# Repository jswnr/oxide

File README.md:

# Oxide
A 60-key USB keyboard built with Raspberry Pi Pico

## Default layout
|         |      |       |      |      |       |       |       |      |      |       |               |
|---------|------|-------|------|------|-------|-------|-------|------|------|-------|---------------|
| \`      | 1 F1 | 2 F2  | 3 F3 | 4 F4 | 5 F5  | 6 F6  | 7 F7  | 8 F8 | 9 F9 | 0 F10 | Backspace F11 |
| Tab     | Q    | W     | E    | R    | T     | Y     | U     | I    | O    | P     | Delete F12    |
| Esc     | A    | S     | D    | F    | G     | H ←   | J ↓   | K ↑  | L →  | ;     | Enter         |
| Shift   | Z    | X     | C    | V    | B     | N     | M     | ,    | .    | /     | '             |
| Control | Fn   | Super | \\   | Alt  | Space | Space | AltGr | [    | ]    | -     | =             |

## Bill of materials
| Component              | Details                          | Quantity |
|------------------------|----------------------------------|----------|
| PCB                    | 1.2 mm thick                     | 1        |
| Raspberry Pi Pico      |                                  | 1        |
| Male pin header        | 2.54 mm pitch, 20 pins           | 2        |
| Cherry MX switch       |                                  | 60       |
| 1N4148 diode           | DO-35 package                    | 60       |
| Case                   | `case.scad`                      | 1        |
| Homing keycap          | `keycap_homing.scad`             | 2        |
| Space keycap           | `keycap_space.scad`              | 2        |
| Keycap                 | `keycap.scad`                    | 56       |
| M2 screw               | Pan head, 6 mm long              | 8        |
| M2 brass insert        | 6 mm long, 3.5 mm outer diameter | 8        |

## Firmware
1. Install Pico SDK and Picotool.
2. Navigate to the `firmware` directory and run:
```
mkdir build
cd build
cmake ..
make -j$(nproc)
```
3. Hold down the BOOTSEL button on the Pico while plugging it in. Then run the following commands as root:
```
picotool load firmware.uf2
picotool reboot
```

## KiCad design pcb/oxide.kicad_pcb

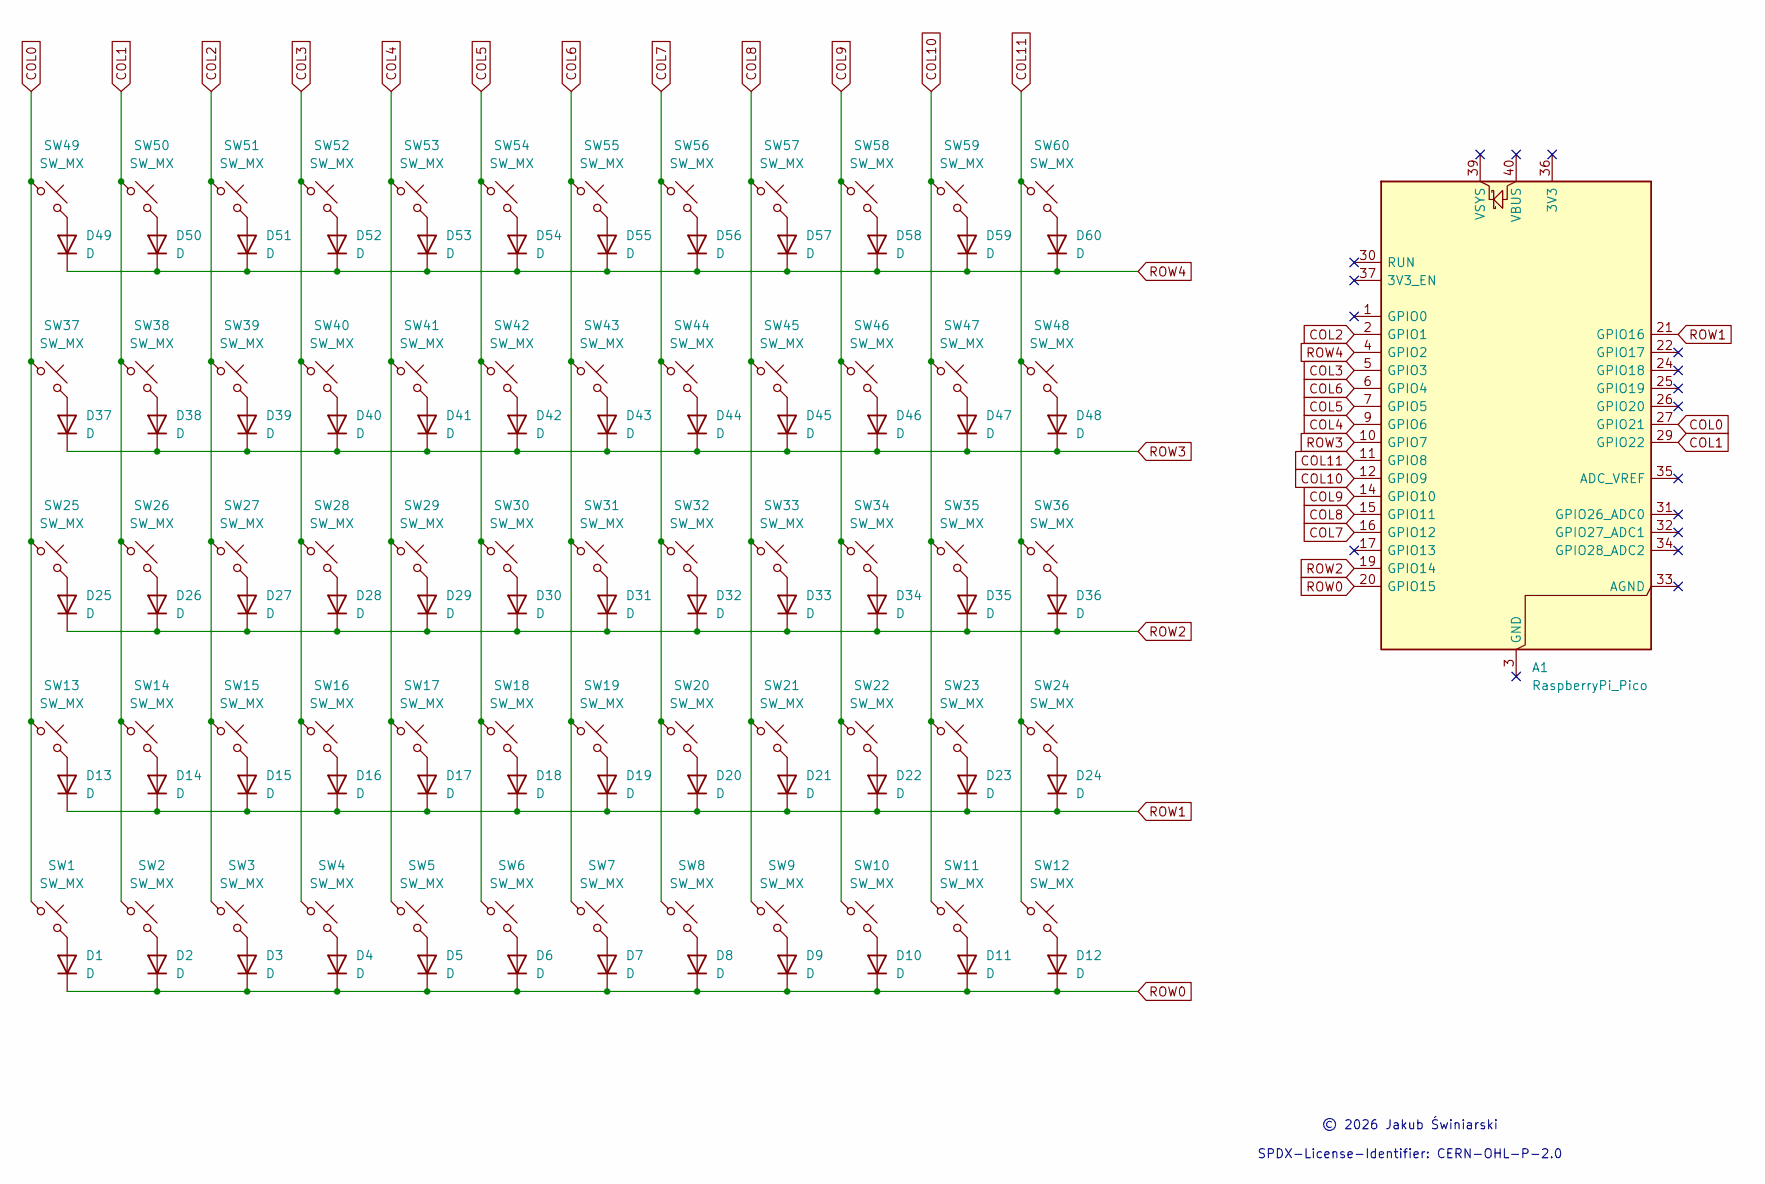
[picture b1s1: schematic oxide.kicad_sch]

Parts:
A1: RaspberryPi_Pico; RaspberryPi_Pico_Common_THT
D1, D2, D3, D4, D5, D6, D7, D8, D9, D10, D11, D12, D13, D14, D15, D16, D17, D18, D19, D20, D21, D22, D23, D24, D25, D26, D27, D28, D29, D30, D31, D32, D33, D34, D35, D36, D37, D38, D39, D40, D41, D42, D43, D44, D45, D46, D47, D48, D49, D50, D51, D52, D53, D54, D55, D56, D57, D58, D59, D60: D; D_DO-35_SOD27_P7.62mm_Horizontal
SW1, SW2, SW3, SW4, SW5, SW6, SW7, SW8, SW9, SW10, SW11, SW12, SW13, SW14, SW15, SW16, SW17, SW18, SW19, SW20, SW21, SW22, SW23, SW24, SW25, SW26, SW27, SW28, SW29, SW30, SW31, SW32, SW33, SW34, SW35, SW36, SW37, SW38, SW39, SW40, SW41, SW42, SW43, SW44, SW45, SW46, SW47, SW48, SW49, SW50, SW51, SW52, SW53, SW54, SW55, SW56, SW57, SW58, SW59, SW60: SW_MX; SW_Cherry_MX_1.00u_PCB

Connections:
COL0: A1.27 (GPIO21), SW1.1, SW13.1, SW25.1, SW37.1, SW49.1
COL1: A1.29 (GPIO22), SW2.1, SW14.1, SW26.1, SW38.1, SW50.1
COL2: A1.2 (GPIO1), SW3.1, SW15.1, SW27.1, SW39.1, SW51.1
COL3: A1.5 (GPIO3), SW4.1, SW16.1, SW28.1, SW40.1, SW52.1
COL4: A1.9 (GPIO6), SW5.1, SW17.1, SW29.1, SW41.1, SW53.1
COL5: A1.7 (GPIO5), SW6.1, SW18.1, SW30.1, SW42.1, SW54.1
COL6: A1.6 (GPIO4), SW7.1, SW19.1, SW31.1, SW43.1, SW55.1
COL7: A1.16 (GPIO12), SW8.1, SW20.1, SW32.1, SW44.1, SW56.1
COL8: A1.15 (GPIO11), SW9.1, SW21.1, SW33.1, SW45.1, SW57.1
COL9: A1.14 (GPIO10), SW10.1, SW22.1, SW34.1, SW46.1, SW58.1
COL10: A1.12 (GPIO9), SW11.1, SW23.1, SW35.1, SW47.1, SW59.1
COL11: A1.11 (GPIO8), SW12.1, SW24.1, SW36.1, SW48.1, SW60.1
unnamed: D1.2 (A), SW1.2
unnamed: D2.2 (A), SW2.2
unnamed: D3.2 (A), SW3.2
unnamed: D4.2 (A), SW4.2
unnamed: D5.2 (A), SW5.2
unnamed: D6.2 (A), SW6.2
unnamed: D7.2 (A), SW7.2
unnamed: D8.2 (A), SW8.2
unnamed: D9.2 (A), SW9.2
unnamed: D10.2 (A), SW10.2
unnamed: D11.2 (A), SW11.2
unnamed: D12.2 (A), SW12.2
unnamed: D13.2 (A), SW13.2
unnamed: D14.2 (A), SW14.2
unnamed: D15.2 (A), SW15.2
unnamed: D16.2 (A), SW16.2
unnamed: D17.2 (A), SW17.2
unnamed: D18.2 (A), SW18.2
unnamed: D19.2 (A), SW19.2
unnamed: D20.2 (A), SW20.2
unnamed: D21.2 (A), SW21.2
unnamed: D22.2 (A), SW22.2
unnamed: D23.2 (A), SW23.2
unnamed: D24.2 (A), SW24.2
unnamed: D25.2 (A), SW25.2
unnamed: D26.2 (A), SW26.2
unnamed: D27.2 (A), SW27.2
unnamed: D28.2 (A), SW28.2
unnamed: D29.2 (A), SW29.2
unnamed: D30.2 (A), SW30.2
unnamed: D31.2 (A), SW31.2
unnamed: D32.2 (A), SW32.2
unnamed: D33.2 (A), SW33.2
unnamed: D34.2 (A), SW34.2
unnamed: D35.2 (A), SW35.2
unnamed: D36.2 (A), SW36.2
unnamed: D37.2 (A), SW37.2
unnamed: D38.2 (A), SW38.2
unnamed: D39.2 (A), SW39.2
unnamed: D40.2 (A), SW40.2
unnamed: D41.2 (A), SW41.2
unnamed: D42.2 (A), SW42.2
unnamed: D43.2 (A), SW43.2
unnamed: D44.2 (A), SW44.2
unnamed: D45.2 (A), SW45.2
unnamed: D46.2 (A), SW46.2
unnamed: D47.2 (A), SW47.2
unnamed: D48.2 (A), SW48.2
unnamed: D49.2 (A), SW49.2
unnamed: D50.2 (A), SW50.2
unnamed: D51.2 (A), SW51.2
unnamed: D52.2 (A), SW52.2
unnamed: D53.2 (A), SW53.2
unnamed: D54.2 (A), SW54.2
unnamed: D55.2 (A), SW55.2
unnamed: D56.2 (A), SW56.2
unnamed: D57.2 (A), SW57.2
unnamed: D58.2 (A), SW58.2
unnamed: D59.2 (A), SW59.2
unnamed: D60.2 (A), SW60.2
ROW0: A1.20 (GPIO15), D1.1 (K), D2.1 (K), D3.1 (K), D4.1 (K), D5.1 (K), D6.1 (K), D7.1 (K), D8.1 (K), D9.1 (K), D10.1 (K), D11.1 (K), D12.1 (K)
ROW1: A1.21 (GPIO16), D13.1 (K), D14.1 (K), D15.1 (K), D16.1 (K), D17.1 (K), D18.1 (K), D19.1 (K), D20.1 (K), D21.1 (K), D22.1 (K), D23.1 (K), D24.1 (K)
ROW2: A1.19 (GPIO14), D25.1 (K), D26.1 (K), D27.1 (K), D28.1 (K), D29.1 (K), D30.1 (K), D31.1 (K), D32.1 (K), D33.1 (K), D34.1 (K), D35.1 (K), D36.1 (K)
ROW3: A1.10 (GPIO7), D37.1 (K), D38.1 (K), D39.1 (K), D40.1 (K), D41.1 (K), D42.1 (K), D43.1 (K), D44.1 (K), D45.1 (K), D46.1 (K), D47.1 (K), D48.1 (K)
ROW4: A1.4 (GPIO2), D49.1 (K), D50.1 (K), D51.1 (K), D52.1 (K), D53.1 (K), D54.1 (K), D55.1 (K), D56.1 (K), D57.1 (K), D58.1 (K), D59.1 (K), D60.1 (K)

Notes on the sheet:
© 2026 Jakub Świniarski SPDX-License-Identifier: CERN-OHL-P-2.0

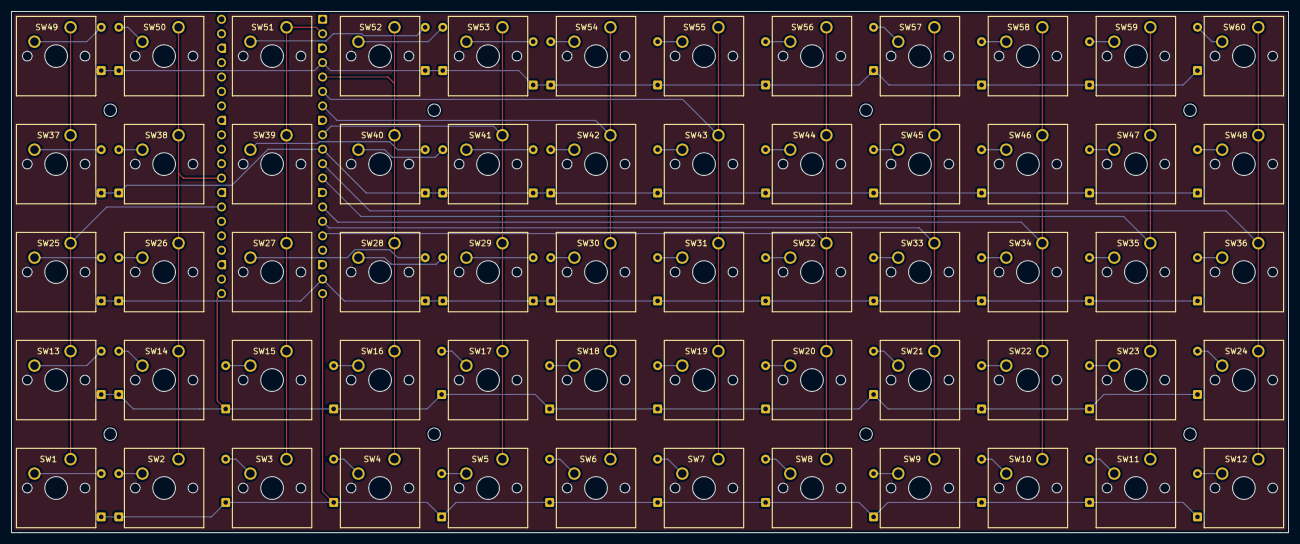
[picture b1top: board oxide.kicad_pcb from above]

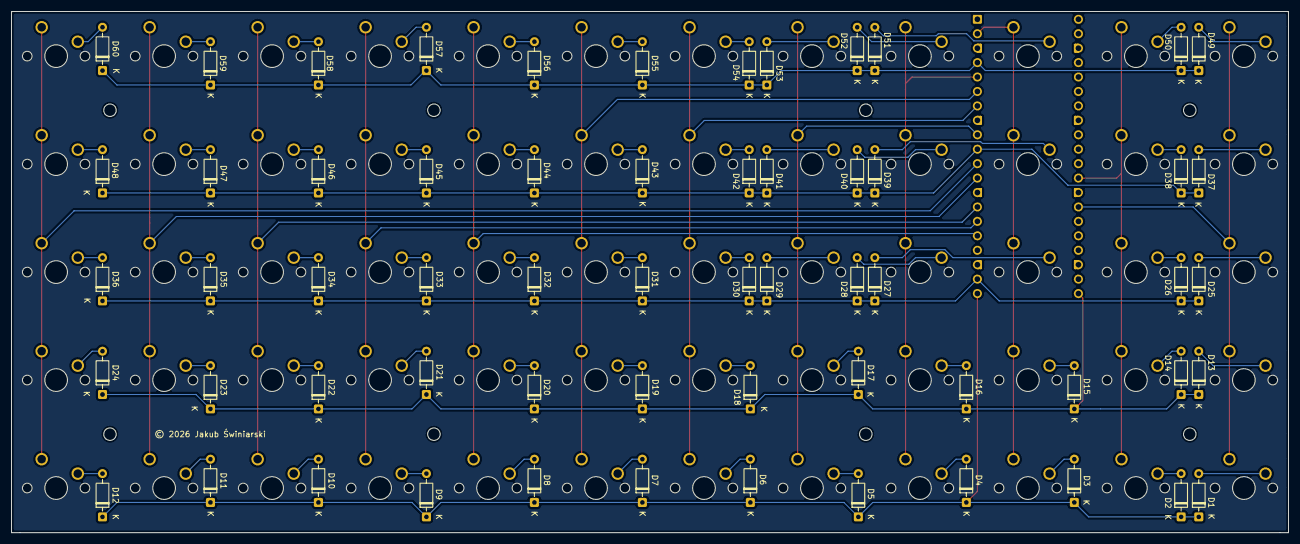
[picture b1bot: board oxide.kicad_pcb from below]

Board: 2 copper layers, 224.7 x 91.7 mm, 121 parts (61 on the bottom side), 77 nets.
